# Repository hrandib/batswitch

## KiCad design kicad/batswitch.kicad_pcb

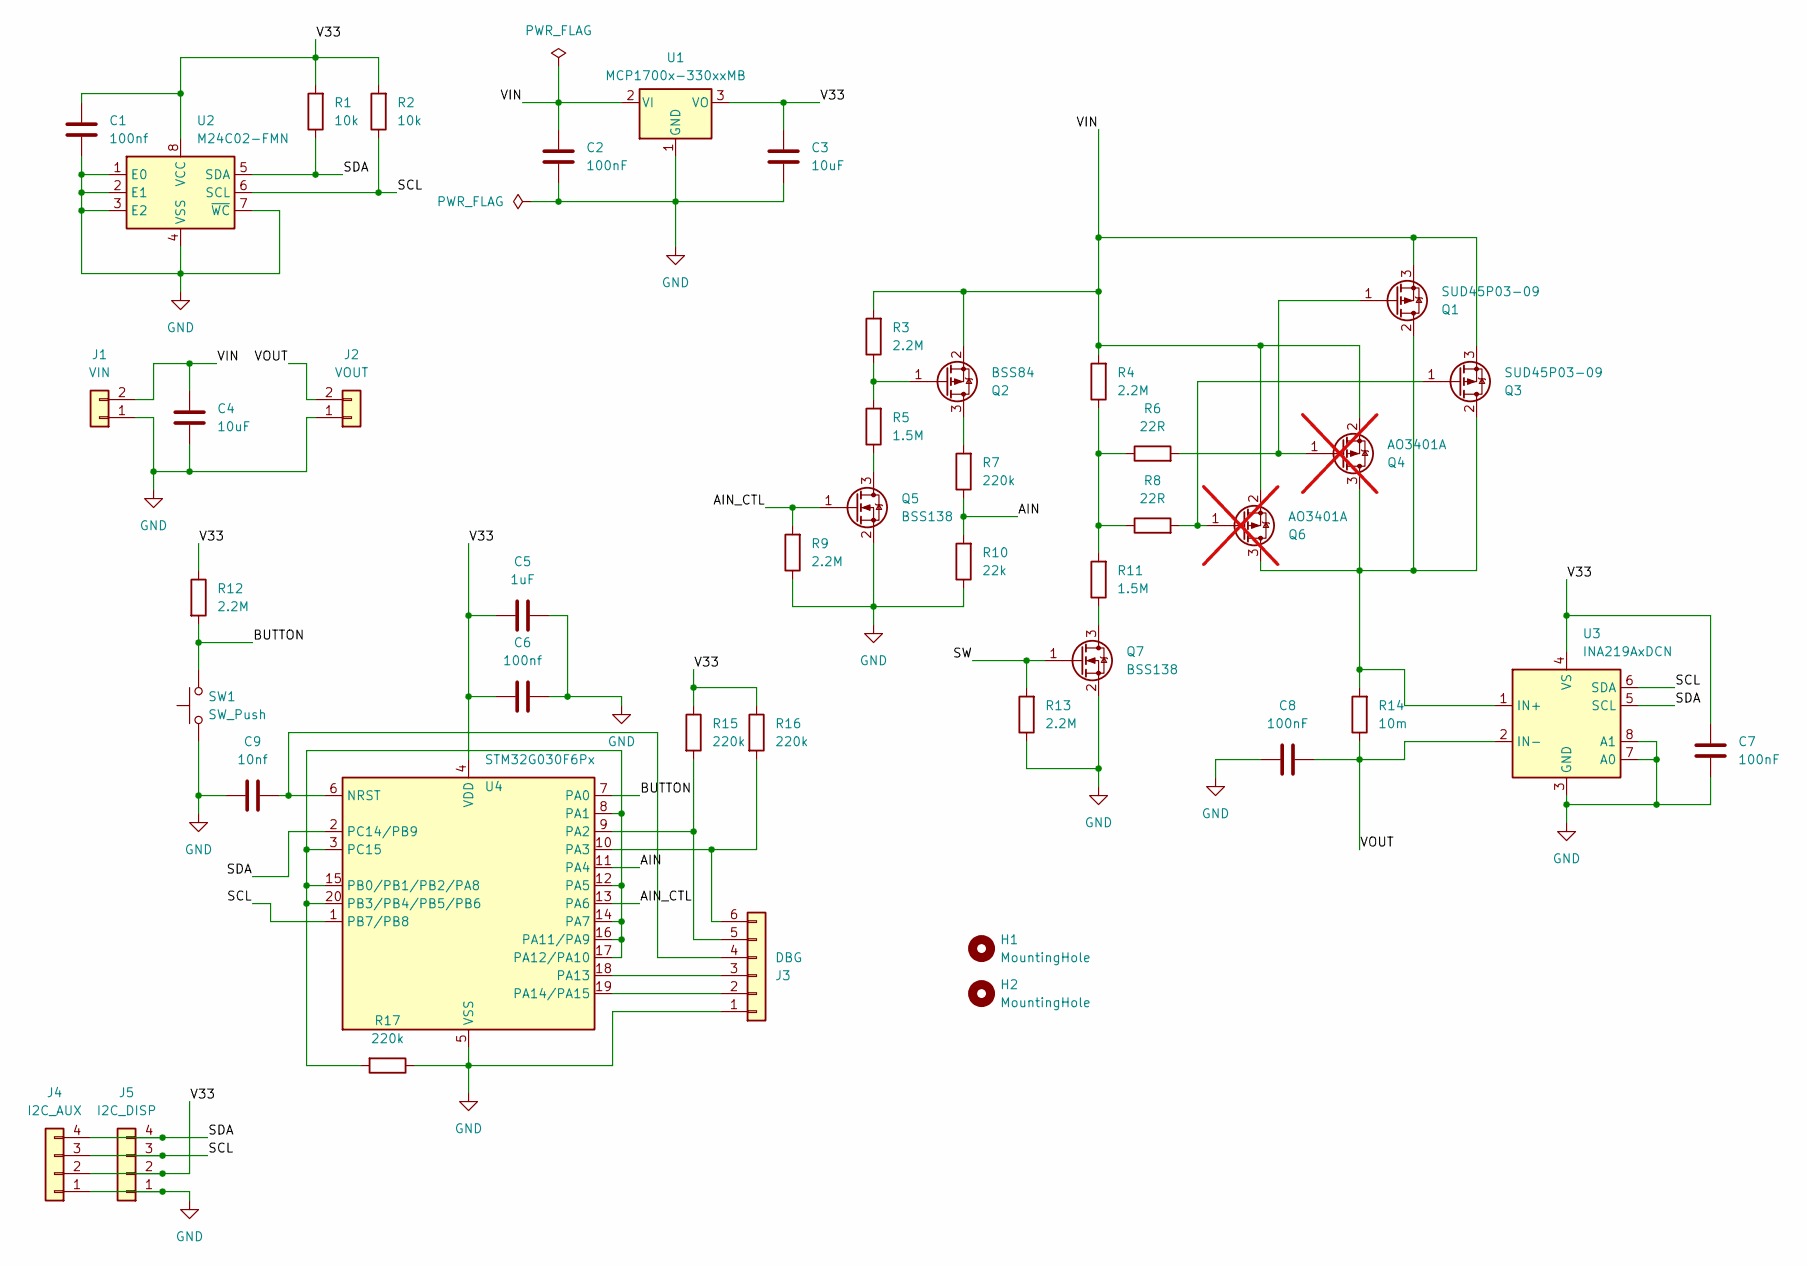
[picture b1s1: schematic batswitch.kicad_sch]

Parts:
C1, C6: 100nf; C_0603_1608Metric
C2, C7, C8: 100nF; C_0603_1608Metric
C3, C4: 10uF; C_1206_3216Metric
C5: 1uF; C_0603_1608Metric
C9: 10nf; C_0603_1608Metric
H1, H2: MountingHole; MountingHole_2.7mm_M2.5
J1: VIN; SolderWire-2.5sqmm_1x02_P7.2mm_D2.4mm_OD3.6mm
J2: VOUT; SolderWire-2.5sqmm_1x02_P7.2mm_D2.4mm_OD3.6mm
J3: DBG; PinHeader_1x06_P1.27mm_Vertical
J4: I2C_AUX; PinHeader_1x04_P2.54mm_Vertical
J5: I2C_DISP; PinHeader_1x04_P2.54mm_Vertical
Q1, Q3: SUD45P03-09; TO-252-2
Q2: BSS84; SOT-23
Q4, Q6: AO3401A; SOT-23; not fitted
Q5, Q7: BSS138; SOT-23
R1, R2: 10k; R_0603_1608Metric
R3, R4, R9, R12, R13: 2.2M; R_0603_1608Metric
R5, R11: 1.5M; R_0603_1608Metric
R6, R8: 22R; R_0603_1608Metric
R7, R15, R16, R17: 220k; R_0603_1608Metric
R10: 22k; R_0603_1608Metric
R14: 10m; R_1206_3216Metric
SW1: SW_Push; SW_Push_1P1T_NO_6x6mm_H9.5mm
U1: MCP1700x-330xxMB; SOT-89-3
U2: M24C02-FMN; SOIC-8_3.9x4.9mm_P1.27mm
U3: INA219AxDCN; SOT-23-8
U4: STM32G030F6Px; TSSOP-20_4.4x6.5mm_P0.65mm

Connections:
/AIN: R7.1, R10.2, U4.11 (PA4)
/AIN_CTL: Q5.1 (G), R9.2, U4.13 (PA6)
/BUTTON: R12.2, SW1.2, U4.7 (PA0)
/SCL: J4.3, J5.3, R2.1, U2.6 (SCL), U3.6 (SDA), U4.1 (PB7/PB8)
/SDA: J4.4, J5.4, R1.1, U2.5 (SDA), U3.5 (SCL), U4.2 (PC14/PB9)
/SW: Q7.1 (G), R13.2
/V33: C1.2, C3.1, C5.1, C6.1, C7.2, J4.2, J5.2, R1.2, R2.2, R12.1, R15.1, R16.1, U1.3 (VO), U2.8 (VCC), U3.4 (VS), U4.4 (VDD)
/VIN: C2.1, C4.1, J1.2, Q1.3 (S), Q2.2 (S), Q3.3 (S), Q4.2 (S), Q6.2 (S), R3.2, R4.2, U1.2 (VI)
/VOUT: C8.1, J2.2, R14.1, U3.2 (IN-)
GND: C1.1, C2.2, C3.2, C4.2, C5.2, C6.2, C7.1, C8.2, C9.1, J1.1, J2.1, J3.1, J4.1, J5.1, Q5.2 (S), Q7.2 (S), R9.1, R10.1, R13.1, R17.1, SW1.1, U1.1 (GND), U2.1 (E0), U2.2 (E1), U2.3 (E2), U2.4 (VSS), U2.7 (~WC), U3.3 (GND), U3.7 (A0), U3.8 (A1), U4.5 (VSS)
unnamed: J3.2, U4.19 (PA14/PA15)
unnamed: J3.3, U4.18 (PA13)
unnamed: C9.2, J3.4, U4.6 (NRST)
unnamed: J3.5, R15.2, U4.9 (PA2)
unnamed: J3.6, R16.2, U4.10 (PA3)
unnamed: Q1.2 (D), Q3.2 (D), Q4.3 (D), Q6.3 (D), R14.2, U3.1 (IN+)
unnamed: Q1.1 (G), Q4.1 (G), R6.2
unnamed: Q2.3 (D), R7.2
unnamed: Q2.1 (G), R3.1, R5.2
unnamed: Q3.1 (G), Q6.1 (G), R8.2
unnamed: Q5.3 (D), R5.1
unnamed: Q7.3 (D), R11.1
unnamed: R4.1, R6.1, R8.1, R11.2
unnamed: R17.2, U4.3 (PC15), U4.8 (PA1), U4.12 (PA5), U4.14 (PA7), U4.15 (PB0/PB1/PB2/PA8), U4.16 (PA11/PA9), U4.17 (PA12/PA10), U4.20 (PB3/PB4/PB5/PB6)

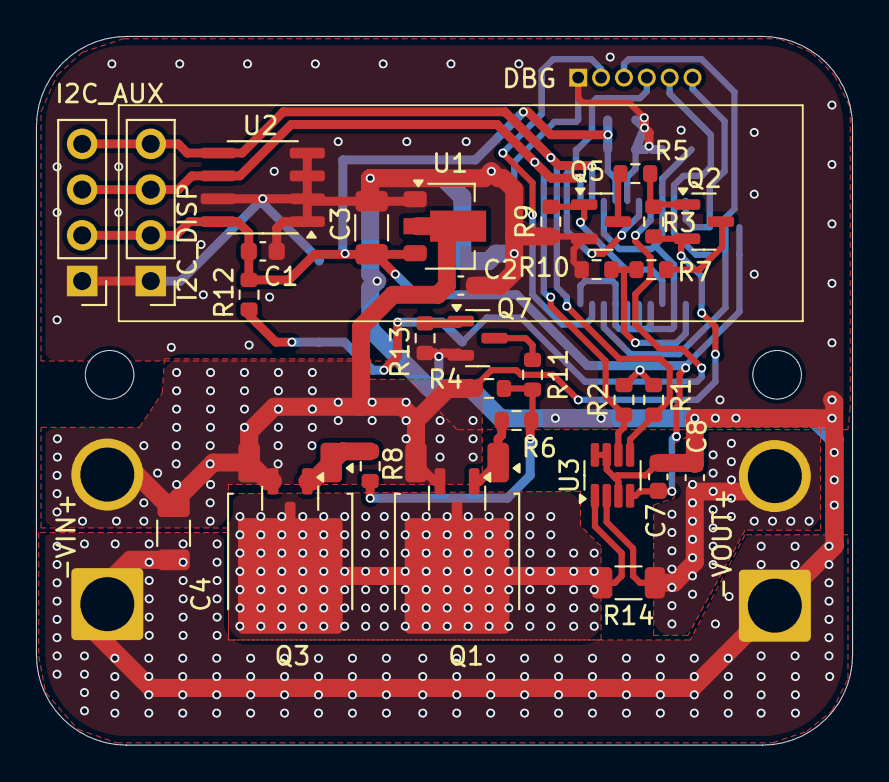
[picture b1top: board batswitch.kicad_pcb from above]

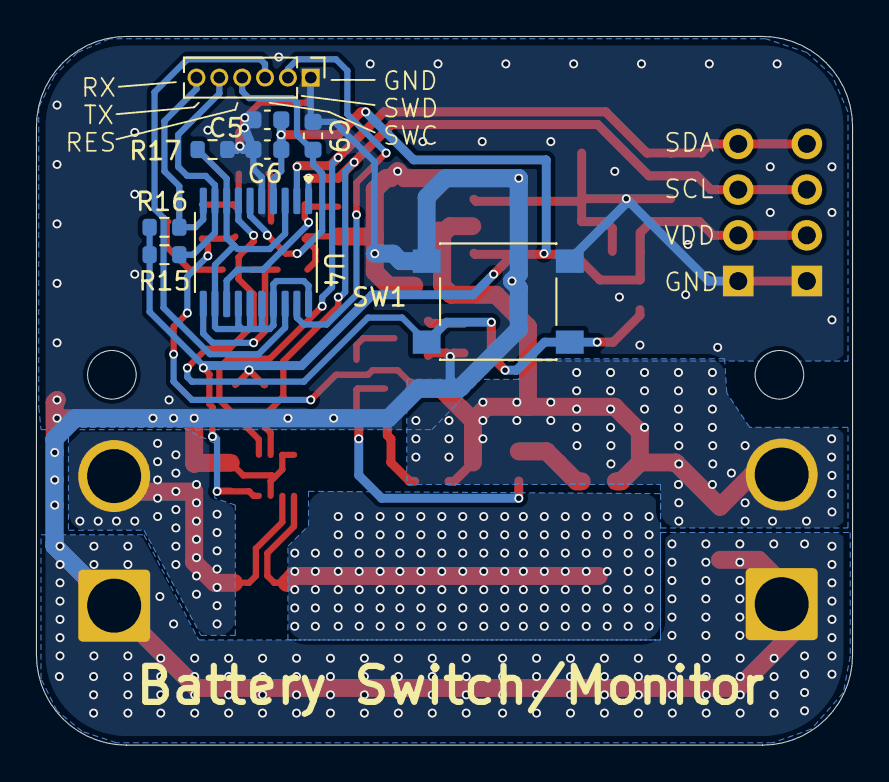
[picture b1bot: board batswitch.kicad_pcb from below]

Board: 2 copper layers, 45.3 x 39.4 mm, 45 parts (9 on the bottom side), 24 nets.

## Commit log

2024-06-09 Add schematics and PCB design
2024-06-09 pcb: Fix ground plane
